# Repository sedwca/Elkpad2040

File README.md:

# Elkpad2040
Untested. RP2040-based numpad with USB passthrough.

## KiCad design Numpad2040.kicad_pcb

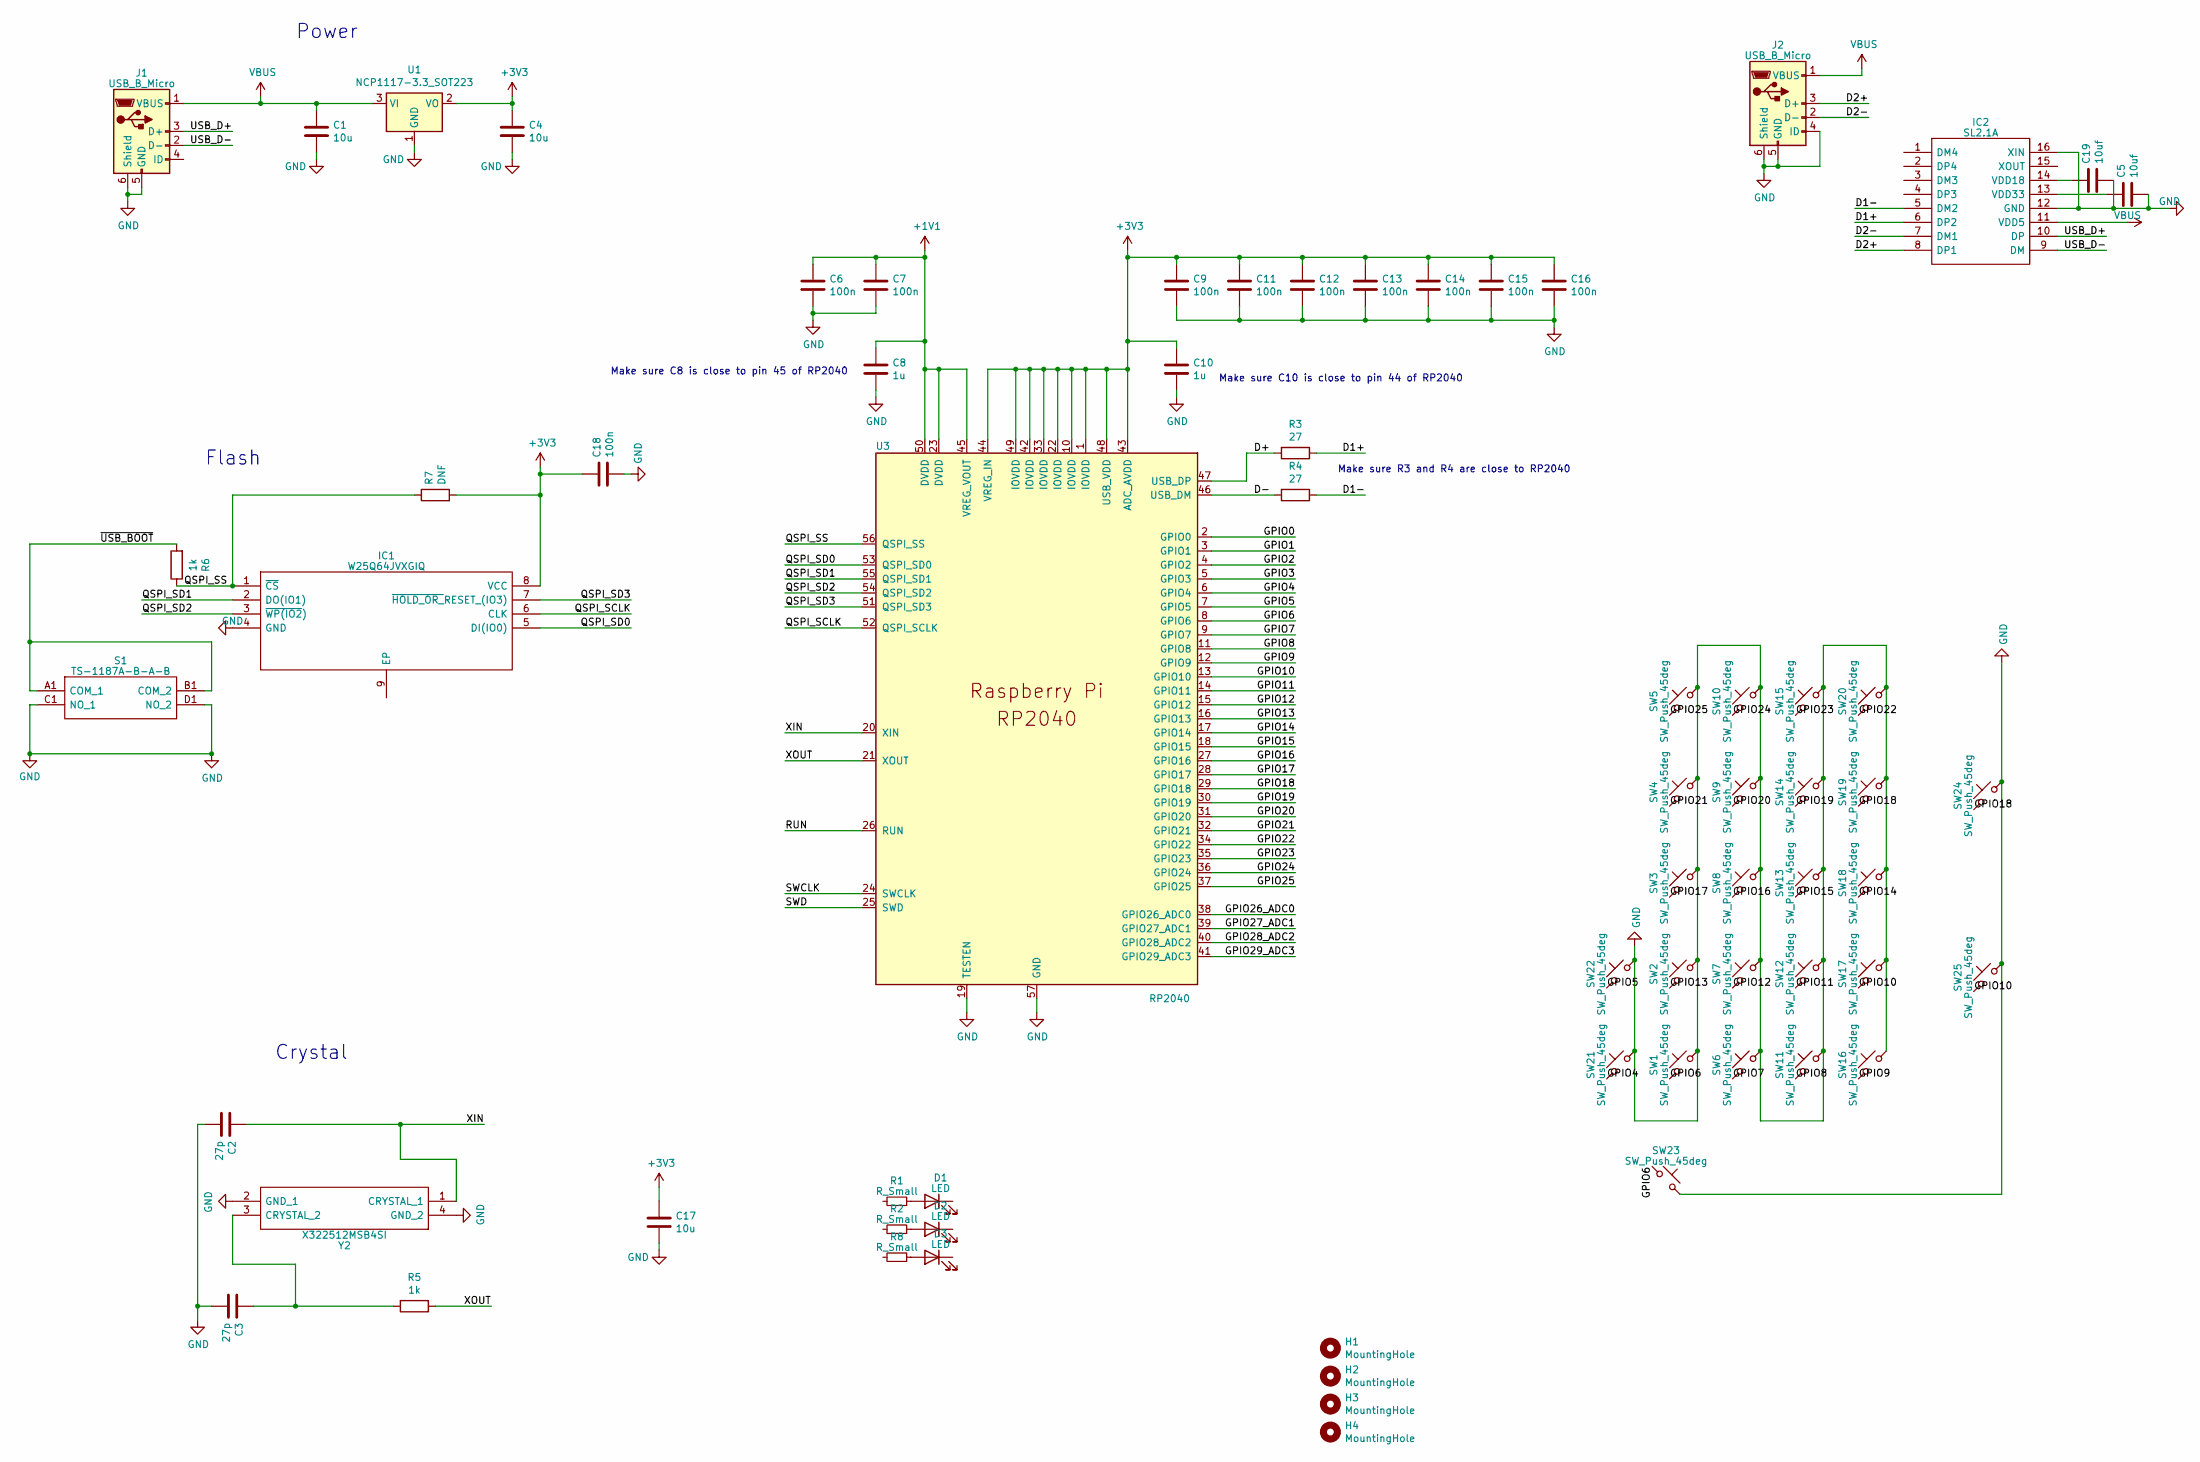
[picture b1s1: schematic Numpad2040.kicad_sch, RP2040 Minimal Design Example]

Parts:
C1, C4, C17: 10u; C_0805_2012Metric
C2, C3: 27p; C_0402_1005Metric
C5, C19: 10uf; C_0402_1005Metric
C6, C7, C9, C11, C12, C13, C14, C15, C16, C18: 100n; C_0402_1005Metric
C8, C10: 1u; C_0402_1005Metric
D1, D2, D3: LED
H1, H2, H3, H4: MountingHole; MountingHole_2.7mm_M2.5
IC1: W25Q64JVXGIQ; SON80P400X400X50-9N; Manufacturer_Part_Number W25Q64JVXGIQ
IC2: SL2.1A; SOIC127P604X185-16N; Manufacturer_Part_Number SL2.1A
J1, J2: USB_B_Micro; USB_Micro-B_Molex-105017-0001
R1, R2, R8: R_Small
R3, R4: 27; C_0402_1005Metric
R5, R6: 1k; C_0402_1005Metric
R7: DNF; R_1206_3216Metric_Pad1.30x1.75mm_HandSolder
S1: TS-1187A-B-A-B; TS1187ABAB; Manufacturer_Part_Number TS-1187A-B-A-B
SW1, SW2, SW3, SW4, SW5, SW6, SW7, SW8, SW9, SW10, SW11, SW12, SW13, SW14, SW15, SW16, SW17, SW18, SW19, SW20, SW21, SW22: SW_Push_45deg; SW_Cherry_MX_PCB_1.00u
SW23, SW24, SW25: SW_Push_45deg; SW_Cherry_MX_PCB_2.00u_90deg
U1: NCP1117-3.3_SOT223; SOT-223-3_TabPin2
U3: RP2040; QFN40P700X700X90-57N-D
Y2: X322512MSB4SI; Manufacturer_Part_Number X322512MSB4SI

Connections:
+1V1: C6.1, C7.1, C8.1, U3.23 (DVDD), U3.45 (VREG_VOUT), U3.50 (DVDD)
+3V3: C4.1, C9.1, C10.1, C11.1, C12.1, C13.1, C14.1, C15.1, C16.1, C17.1, C18.1, IC1.8 (VCC), R7.2, U1.2 (VO), U3.1 (IOVDD), U3.10 (IOVDD), U3.22 (IOVDD), U3.33 (IOVDD), U3.42 (IOVDD), U3.43 (ADC_AVDD), U3.44 (VREG_IN), U3.48 (USB_VDD), U3.49 (IOVDD)
/D1+: IC2.6 (DP2), R3.1
/D1-: IC2.5 (DM2), R4.1
/D2+: IC2.8 (DP1), J2.3 (D+)
/D2-: IC2.7 (DM1), J2.2 (D-)
/D+: R3.2, U3.47 (USB_DP)
/D-: R4.2, U3.46 (USB_DM)
/GPIO0: U3.2 (GPIO0)
/GPIO1: U3.3 (GPIO1)
/GPIO2: U3.4 (GPIO2)
/GPIO3: U3.5 (GPIO3)
/GPIO4: SW21.1, U3.6 (GPIO4)
/GPIO5: SW22.1, U3.7 (GPIO5)
/GPIO6: SW1.1, SW23.1, U3.8 (GPIO6)
/GPIO7: SW6.1, U3.9 (GPIO7)
/GPIO8: SW11.1, U3.11 (GPIO8)
/GPIO9: SW16.1, U3.12 (GPIO9)
/GPIO10: SW17.1, SW25.1, U3.13 (GPIO10)
/GPIO11: SW12.1, U3.14 (GPIO11)
/GPIO12: SW7.1, U3.15 (GPIO12)
/GPIO13: SW2.1, U3.16 (GPIO13)
/GPIO14: SW18.1, U3.17 (GPIO14)
/GPIO15: SW13.1, U3.18 (GPIO15)
/GPIO16: SW8.1, U3.27 (GPIO16)
/GPIO17: SW3.1, U3.28 (GPIO17)
/GPIO18: SW19.1, SW24.1, U3.29 (GPIO18)
/GPIO19: SW14.1, U3.30 (GPIO19)
/GPIO20: SW9.1, U3.31 (GPIO20)
/GPIO21: SW4.1, U3.32 (GPIO21)
/GPIO22: SW20.1, U3.34 (GPIO22)
/GPIO23: SW15.1, U3.35 (GPIO23)
/GPIO24: SW10.1, U3.36 (GPIO24)
/GPIO25: SW5.1, U3.37 (GPIO25)
/GPIO26_ADC0: U3.38 (GPIO26_ADC0)
/GPIO27_ADC1: U3.39 (GPIO27_ADC1)
/GPIO28_ADC2: U3.40 (GPIO28_ADC2)
/GPIO29_ADC3: U3.41 (GPIO29_ADC3)
/QSPI_SCLK: IC1.6 (CLK), U3.52 (QSPI_SCLK)
/QSPI_SD0: IC1.5 (DI(IO0)), U3.53 (QSPI_SD0)
/QSPI_SD1: IC1.2 (DO(IO1)), U3.55 (QSPI_SD1)
/QSPI_SD2: IC1.3 (~WP(IO2)), U3.54 (QSPI_SD2)
/QSPI_SD3: IC1.7 (~HOLD_OR_RESET_(IO3)), U3.51 (QSPI_SD3)
/QSPI_SS: IC1.1 (~CS), R6.1, R7.1, U3.56 (QSPI_SS)
/RUN: U3.26 (RUN)
/SWCLK: U3.24 (SWCLK)
/SWD: U3.25 (SWD)
/USB_D+: IC2.10 (DP), J1.3 (D+)
/USB_D-: IC2.9 (DM), J1.2 (D-)
/XIN: C2.1, U3.20 (XIN), Y2.1 (CRYSTAL_1)
/XOUT: R5.1, U3.21 (XOUT)
/~USB_BOOT: R6.2, S1.A1 (COM_1), S1.B1 (COM_2)
GND: C1.2, C2.2, C3.2, C4.2, C5.2, C6.2, C7.2, C8.2, C9.2, C10.2, C11.2, C12.2, C13.2, C14.2, C15.2, C16.2, C17.2, C18.2, C19.2, IC1.4 (GND), IC2.12 (GND), IC2.16 (XIN), J1.5 (GND), J1.6 (Shield), J2.4 (ID), J2.5 (GND), J2.6 (Shield), S1.C1 (NO_1), S1.D1 (NO_2), SW1.2, SW2.2, SW3.2, SW4.2, SW5.2, SW6.2, SW7.2, SW8.2, SW9.2, SW10.2, SW11.2, SW12.2, SW13.2, SW14.2, SW15.2, SW16.2, SW17.2, SW18.2, SW19.2, SW20.2, SW21.2, SW22.2, SW23.2, SW24.2, SW25.2, U1.1 (GND), U3.19 (TESTEN), U3.57 (GND), Y2.2 (GND_1), Y2.4 (GND_2)
unnamed: D1.2 (A), R1.1
unnamed: D2.2 (A), R2.1
unnamed: D3.2 (A), R8.1
unnamed: C19.1, IC2.14 (VDD18)
unnamed: C5.1, IC2.13 (VDD33)
unnamed: C3.1, R5.2, Y2.3 (CRYSTAL_2)
VBUS: C1.1, IC2.11 (VDD5), J1.1 (VBUS), J2.1 (VBUS), U1.3 (VI)

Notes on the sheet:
Make sure C10 is close to pin 44 of RP2040
Power
Crystal
Make sure R3 and R4 are close to RP2040
Make sure C8 is close to pin 45 of RP2040
Flash

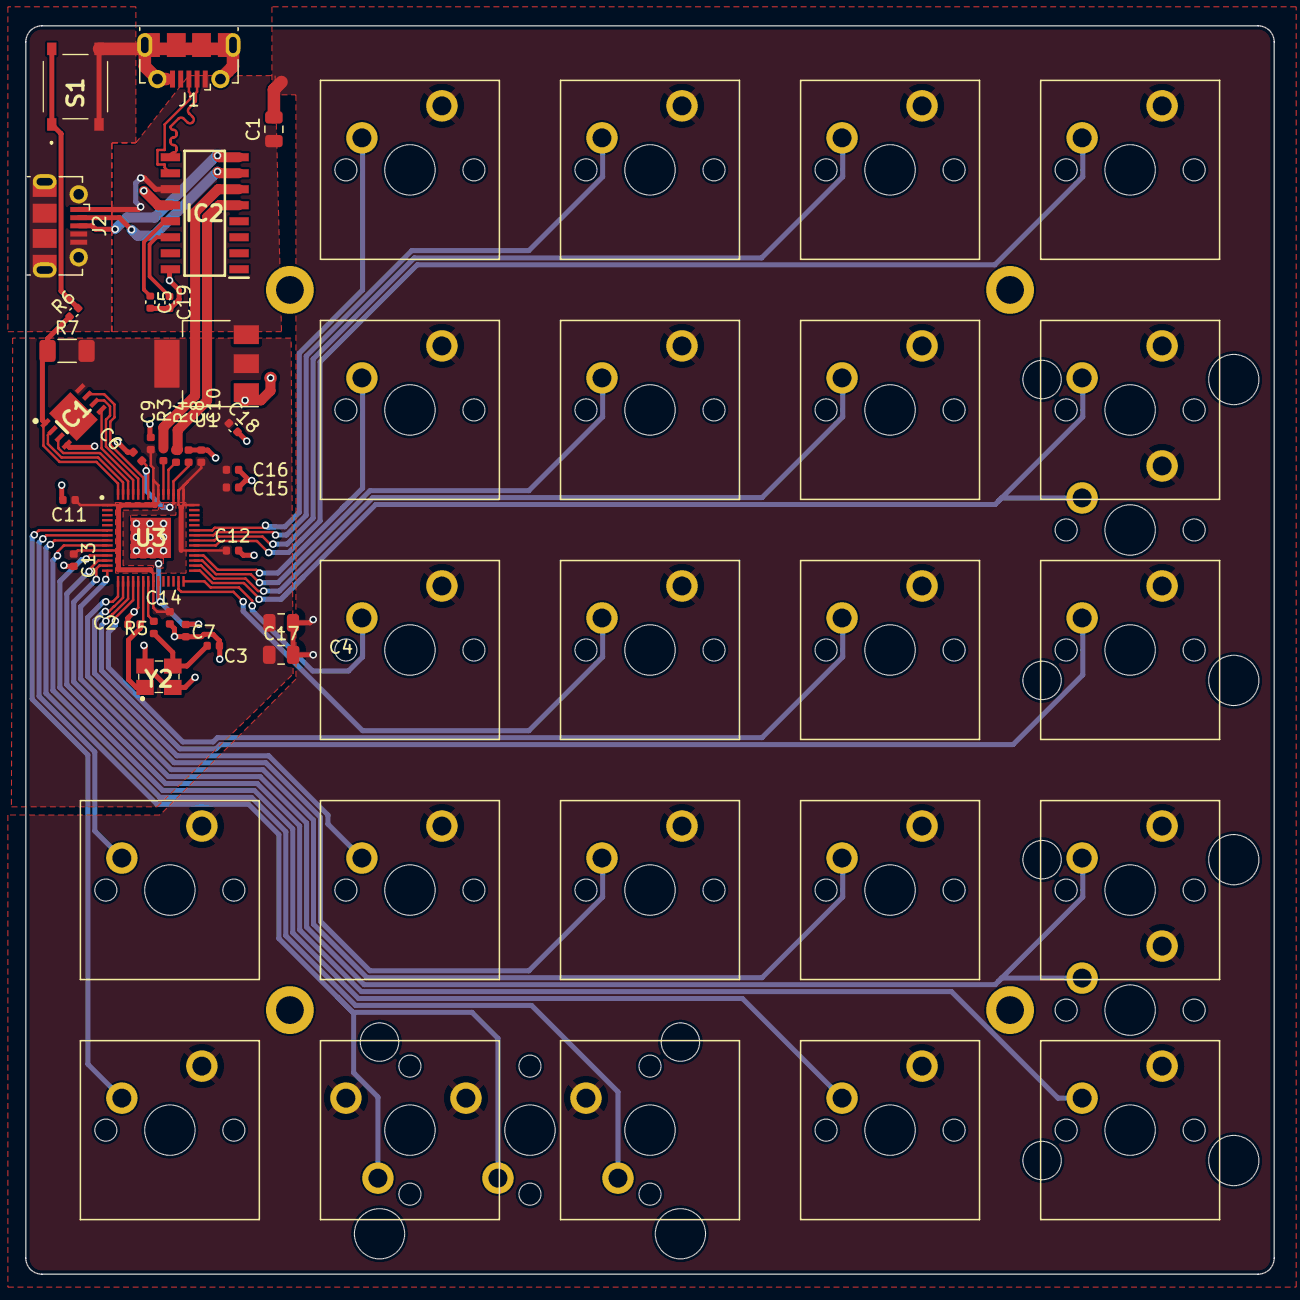
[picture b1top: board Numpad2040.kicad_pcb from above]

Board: 2 copper layers, 99.1 x 99.1 mm, 61 parts (0 on the bottom side), 46 nets.

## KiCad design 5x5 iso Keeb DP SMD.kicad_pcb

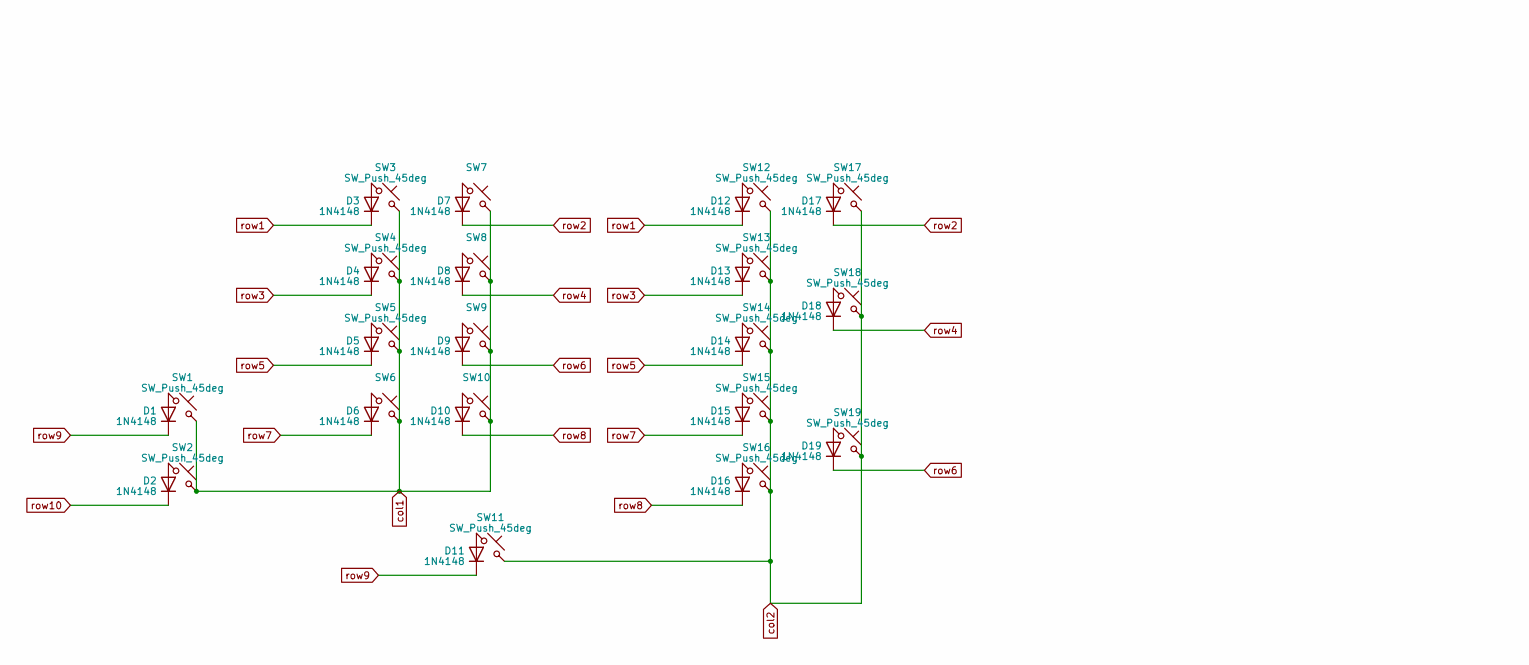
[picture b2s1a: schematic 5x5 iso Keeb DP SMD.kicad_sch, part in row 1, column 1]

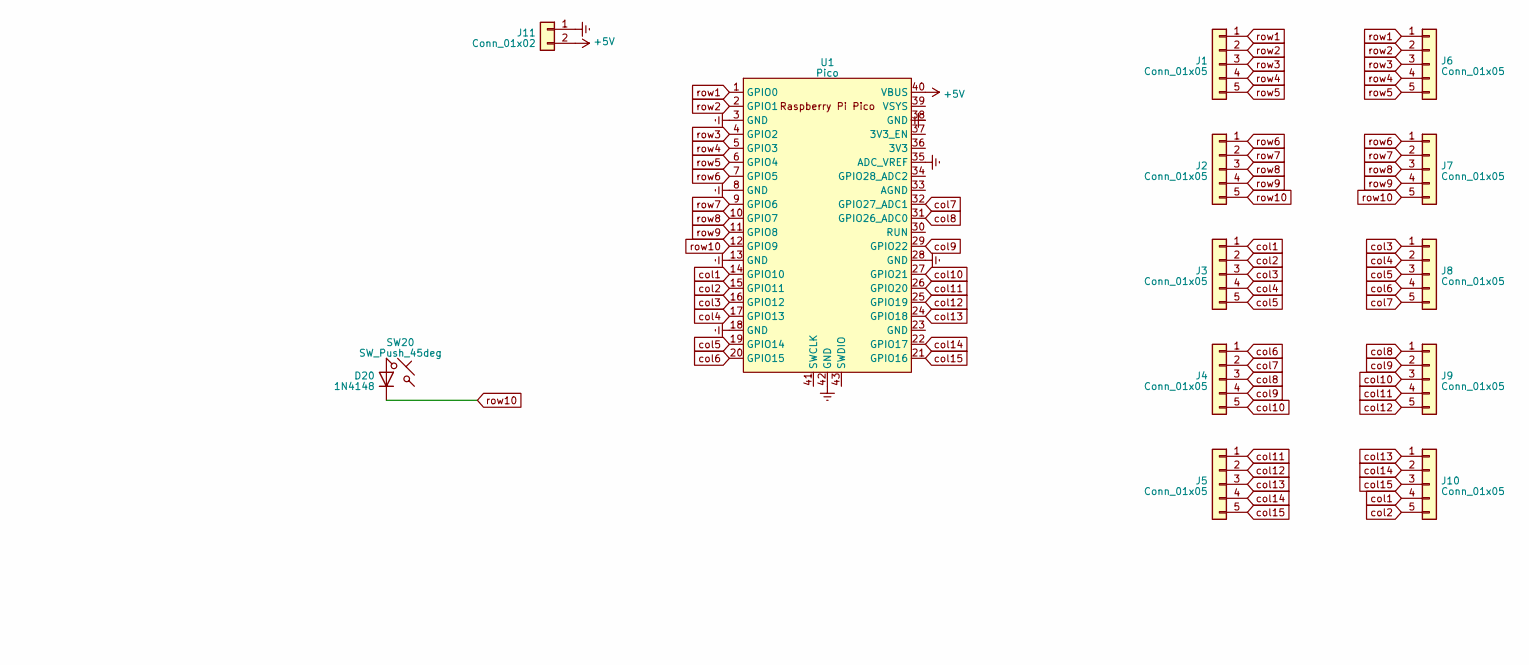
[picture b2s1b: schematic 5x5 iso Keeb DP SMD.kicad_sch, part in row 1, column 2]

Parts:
D1, D2, D3, D4, D5, D6, D7, D8, D9, D10, D11, D12, D13, D14, D15, D16, D17, D18, D19, D20: 1N4148; D_DO-35_SOD27_P7.62mm_Horizontal_no_front_silk
J1, J2, J3, J4, J5, J6, J7, J8, J9, J10: Conn_01x05; PinHeader_1x05_P2.54mm_Vertical Bottom Only
J11: Conn_01x02; JST_EH_B2B-EH-A_1x02_P2.50mm_Vertical
SW1, SW2, SW3, SW4, SW5, SW6, SW7, SW8, SW9, SW10, SW12, SW13, SW14, SW15, SW16, SW17, SW20: SW_Push_45deg; SW_Cherry_MX_PCB_1.00u
SW11: SW_Push_45deg; SW_Cherry_MX_PCB_2.00u
SW18, SW19: SW_Push_45deg; SW_Cherry_MX_PCB_2.00u_90deg
U1: Pico; RPi_Pico_SMD_TH

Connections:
+5V: J11.2, U1.40 (VBUS)
Earth: J11.1, U1.3 (GND), U1.8 (GND), U1.13 (GND), U1.18 (GND), U1.28 (GND), U1.35 (ADC_VREF), U1.38 (GND), U1.42 (GND)
unnamed: D1.2 (A), SW1.1
unnamed: D2.2 (A), SW2.1
unnamed: D3.2 (A), SW3.1
unnamed: D4.2 (A), SW4.1
unnamed: D5.2 (A), SW5.1
unnamed: D6.2 (A), SW6.1
unnamed: D7.2 (A), SW7.1
unnamed: D8.2 (A), SW8.1
unnamed: D9.2 (A), SW9.1
unnamed: D10.2 (A), SW10.1
unnamed: D11.2 (A), SW11.1
unnamed: D12.2 (A), SW12.1
unnamed: D13.2 (A), SW13.1
unnamed: D14.2 (A), SW14.1
unnamed: D15.2 (A), SW15.1
unnamed: D16.2 (A), SW16.1
unnamed: D17.2 (A), SW17.1
unnamed: D18.2 (A), SW18.1
unnamed: D19.2 (A), SW19.1
unnamed: D20.2 (A), SW20.1
col1: J3.1, J10.4, SW1.2, SW2.2, SW3.2, SW4.2, SW5.2, SW6.2, SW7.2, SW8.2, SW9.2, SW10.2, U1.14 (GPIO10)
col2: J3.2, J10.5, SW11.2, SW12.2, SW13.2, SW14.2, SW15.2, SW16.2, SW17.2, SW18.2, SW19.2, U1.15 (GPIO11)
col3: J3.3, J8.1, U1.16 (GPIO12)
col4: J3.4, J8.2, U1.17 (GPIO13)
col5: J3.5, J8.3, U1.19 (GPIO14)
col6: J4.1, J8.4, U1.20 (GPIO15)
col7: J4.2, J8.5, U1.32 (GPIO27_ADC1)
col8: J4.3, J9.1, U1.31 (GPIO26_ADC0)
col9: J4.4, J9.2, U1.29 (GPIO22)
col10: J4.5, J9.3, U1.27 (GPIO21)
col11: J5.1, J9.4, U1.26 (GPIO20)
col12: J5.2, J9.5, U1.25 (GPIO19)
col13: J5.3, J10.1, U1.24 (GPIO18)
col14: J5.4, J10.2, U1.22 (GPIO17)
col15: J5.5, J10.3, U1.21 (GPIO16)
row1: D3.1 (K), D12.1 (K), J1.1, J6.1, U1.1 (GPIO0)
row2: D7.1 (K), D17.1 (K), J1.2, J6.2, U1.2 (GPIO1)
row3: D4.1 (K), D13.1 (K), J1.3, J6.3, U1.4 (GPIO2)
row4: D8.1 (K), D18.1 (K), J1.4, J6.4, U1.5 (GPIO3)
row5: D5.1 (K), D14.1 (K), J1.5, J6.5, U1.6 (GPIO4)
row6: D9.1 (K), D19.1 (K), J2.1, J7.1, U1.7 (GPIO5)
row7: D6.1 (K), D15.1 (K), J2.2, J7.2, U1.9 (GPIO6)
row8: D10.1 (K), D16.1 (K), J2.3, J7.3, U1.10 (GPIO7)
row9: D1.1 (K), D11.1 (K), J2.4, J7.4, U1.11 (GPIO8)
row10: D2.1 (K), D20.1 (K), J2.5, J7.5, U1.12 (GPIO9)

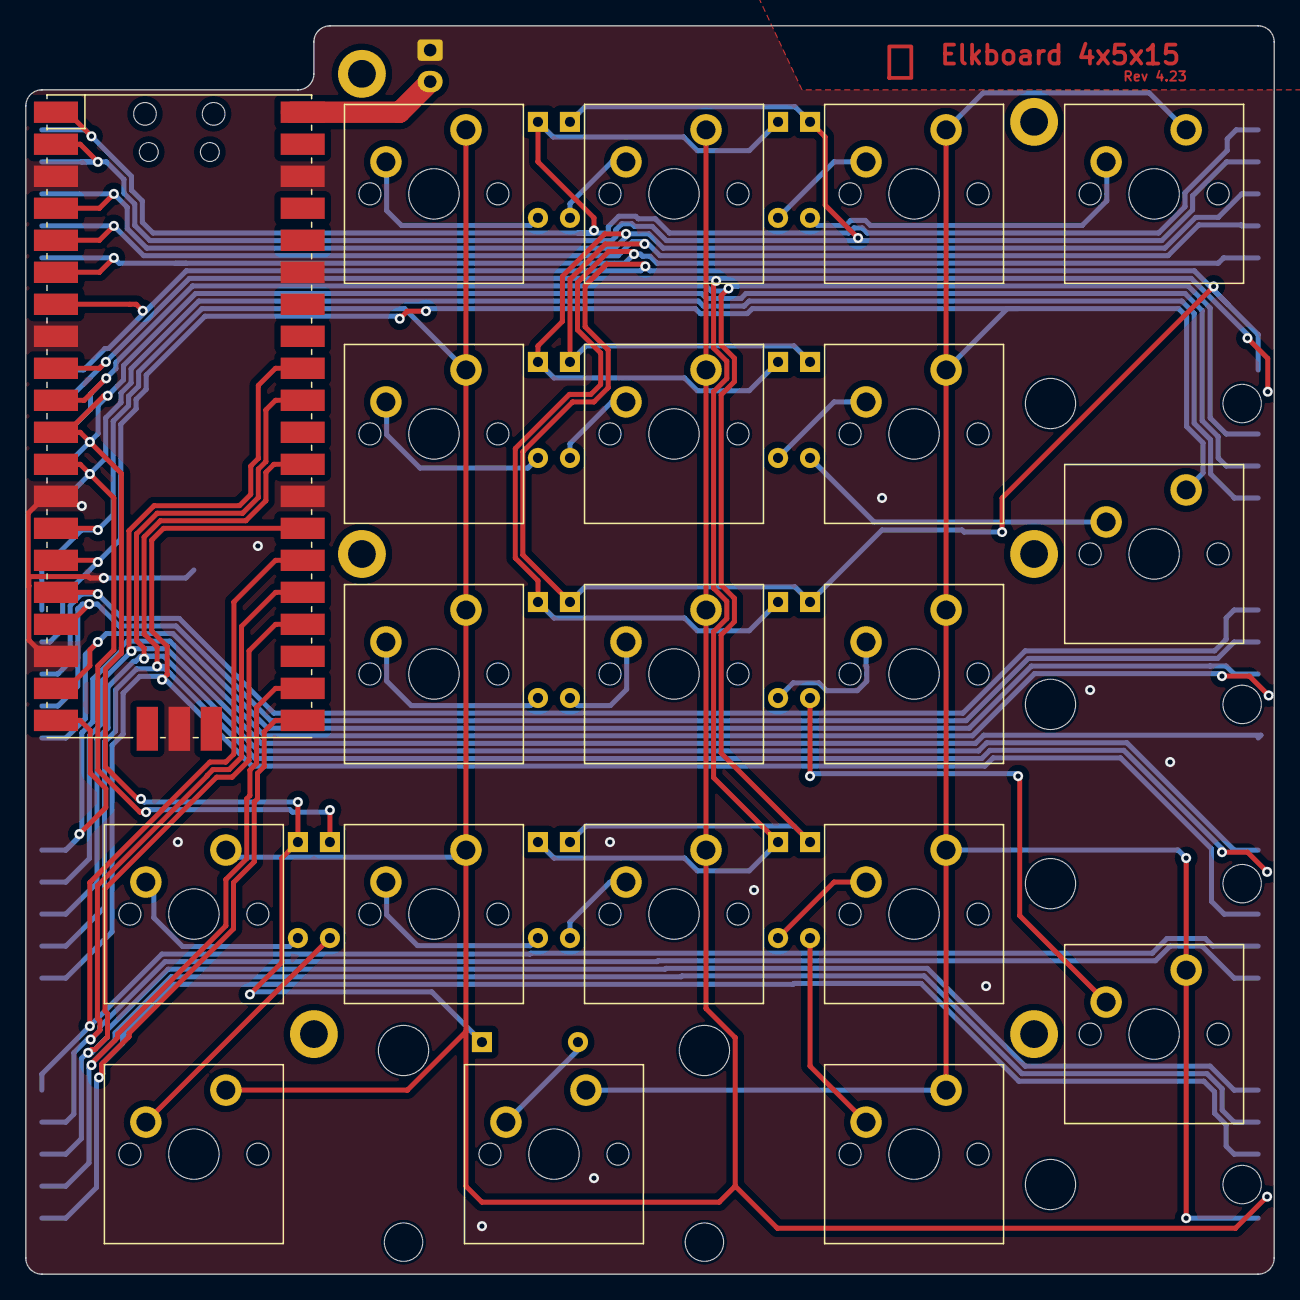
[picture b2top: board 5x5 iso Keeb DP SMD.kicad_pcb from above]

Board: 2 copper layers, 99.1 x 99.1 mm, 50 parts (1 on the bottom side), 46 nets.

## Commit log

2023-05-03 Initial Upload
2023-05-04 Fixed Upload
